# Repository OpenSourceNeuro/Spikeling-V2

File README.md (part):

<p align="left">

<h1 align="center"> Spikeling V 2.2</h1></p>
<h3 align="center">  A hardware implementation of spiking neurons for neuroscience teaching and outreach</h3></p>
<p align="center"><h6 align="right">developed by M.J.Y. Zimmermann, A.M. Chagas & T. Baden</h6></p>

<br></br>

This project is licensed under the [GNU General Public License v3.0](https://github.com/OpenSourceNeuro/Spikeling-V2/blob/main/LICENSE)<br>
The hardware is licensed under the [CERN OHL v1.2](https://github.com/OpenSourceNeuro/Spikeling-V2/blob/main/PCB%20-%202.2c/LICENSE)

***

<p style='text-align: justify;'>
Understanding how neurons encode and compute information is fundamental to our study of the brain, but opportunities for hands-on experience with neurophysiological techniques on living neurons are scarce in science education.

<p style='text-align: justify;'>
Due to budgetary constraints and logistical hurdles, few students can be afforded the opportunity to experience electrophysiological recordings on living neurons in action. Yet, a fundamental aspect of neuroscience courses is to understand electrical signalling within neurons and the transmission of signals across synapses, as well as the experimental techniques necessary to observe these properties.

<p style='text-align: justify;'>
To support university-level neuroscience teaching, we designed ‘Spikeling’, an open-source teaching support device that mimics the electrical properties of spiking neurons by running the computationally efficient yet versatile Izhikevich model.

<p style='text-align: justify;'>
It is an artificial neuron that can receive different inputs, integrate them and outputs its computation, just like a spiking neuron would!

<p style='text-align: justify;'>
Technically, it consists on a microcontroller (an ESP32) running the computationally efficient Izhikevich model of a spiking neuron.

<br>

<div>

<h6 align="center">Left: Rendering of spikeling electronic components. Right: Acrylic cover detailing spikeling functionalities.</h6>

</div>

<div>

<p style='text-align: justify;'>
The spikeling project emerged from local needs to teach neuroscience class modules for direct interaction with neuron physiology, data analysis, fluorescence imaging, protocol design, etc. The aim is to provide hands-on experience on how neurons encode information and how diverse variables modulates their activities, while engaging students with crucial aspects of data collection, experimental limitations, methodology and statistical analysis.

<p style='text-align: justify;'>
In order to give users a full interactive experience with the Spikeling neuron, a drawing engraved on the cover details in a neuro-morphic fashion all device functionalities. Furthermore, a spike-triggered LED and buzzer have been added to the device.

<p style='text-align: justify;'>
A dedicated GUI (Graphical User Interface) allows users to fully interact with Spikeling, plot all data generated and record them for further analysis.

<p style='text-align: justify;'>
Overall, Spikeling is a versatile device, allowing any teaching staff to conceive dry-lab tutorials or home assignments related to their own teaching course materials.

<p style='text-align: justify;'>
Enthusiasts and potential collaborators can source the electronic bits for this project from <a href="https://kitspace.org/boards/github.com/maxzimmer/spikeling-v2/">KitSpace</a></p>

</div>

***

<h2 align="center"> A brief summary of Spikeling functions</h3>

<br>

<div>

<h3 align="left"> Neurophysiology:</h3></p>

<p style='text-align: justify;'>
Spikeling is conceived on the Izhikevich model, which “reproduces spiking and bursting behaviour of known type of cortical neurons. The model combines the biologically plausibility of Hodgkin-Huxley-type dynamics and the computational efficiency of integrate-and-fire neurons” (E.M. Izhikevich, IEEE Transactions on Neural Networks, 2003, doi: 10.1109/TNN.2003.820440).

<p style='text-align: justify;'>
Students can appreciate playing with many variables that can be encountered in textbook or related to class material. A simulated patch-clamp experiment (represented by a pipette drawing on the top cover) allows students to “inject current” into the Spikeling neuron. They can furthermore modulate the amount of current injected, the speed and duration at which it is injected and observe the adaptation effect on a spiking neuron.

<p style='text-align: justify;'>
Spikeling also possesses a photodiode (modelized on the top cover as a photoreceptor) making Spikeling photo-sensitive. The photodiode mimics current inputs a photoreceptor would have on a spiking neuron. Students can appreciate the impact of a flash light onto the photoreceptor and investigate the different effects it may have. Ultimately, a supplied LED can be connected to the stimulus port and can then be controlled in frequency and intensity for controlled experiments. Advanced variable such as photoreceptor decay and recovery rate could also be investigated.

<p style='text-align: justify;'>
Each Spikeling unit possesses one “axonal” output and two “dendritic” inputs. Each dendritic input possesses a knob that can modulate the synaptic gain positively or negatively (mimicking excitatory and inhibitory synapses). In advanced stages, students could be encouraged to form neuronal networks. Auxiliary neurons can furthermore be stimulated synchronously from the “main neuron” experiment box to set a controlled environment.

</div>

<br>

<div>

<h6 align="center">Left: A Spikeling unit being stimulated by a direct current injection (blue cable) while receiving synaptic inputs from a second unit (pink cable). Right: Spikeling GUI displaying the unit membrane voltage (red trace) while being light-stimulated by a controlled LED (blue trace) which generates input current (green trace).</h6>

</div>

<br>

***

<br>

<div>

<h3 align="left"> Data analysis</h3></p>

<p style='text-align: justify;'>
Handling large dataset is an important part of daily academic work. However, few universities offer coding and programming modules for their neuroscience courses. A proper data analysis of any kind starts with the understanding of a program language and the understanding of every steps of the analysis pipeline. Only then, students can appreciate the results of their experiments and engage in their critical interpretation.

<p style='text-align: justify;'>
Any data generated by Spikeling can be saved and exported.  The GUI comes with a simple built-in data analysis that allows students to check their data and generate raster plots. From this simple analysis they could appreciate how neuronal information is encoded within stochastic spike trains (see below).

<p style='text-align: justify;'>
This simple analysis could be used for home assignments in the early stages of student degree before engaging them in developing their own analysis code.

<p style='text-align: justify;'>
For advanced data analysis and basic statistics, python notebooks are provided to serve as template for the teaching staff. It is our hope to create a Spikeling community where users could share courses, exercises and data analysis scripts to be widely used in neuroscience and coding courses.

</div>

<br>

<div>

<h6 align="center">GUI displaying the “Neuron Generator” page where users can appreciate the model underlying Spikeling activity and from which they can generate unique neuron to further run on Spikeling.</h6>

</div>

<br>

***

<br>

<div>

<h3 align="left">Stimulus generator:</h3>

<p style='text-align: justify;'>
Spikeling comes by default with a repeated square wave pattern stimulus, on which the user could only modulate the intensity and the frequency, might it be for direct current injection or light stimulation.

<p style='text-align: justify;'>
Here users are encouraged to develop their own stimulus (successive waves, sinusoidal loops, chirp, binary noise, etc.). Some basic stimuli are already available. The main point of this feature is to encourage the students to conceive their own experiments leading them to think about the protocol that needs to be implemented in order to answer the experimental questions they are being faced with.

</div>

<br>

<div>

<h6 align="center">GUI displaying the “Simulus Generator” page where users can generate their own unique stimuli. The left screen shows repetitive increments of current, as seen in classic electrophysiology experiments (10 steps with 10 a.u. current increment lasting 25 ms with a resting period of 5ms at 0 a.u. current). The right screen shows a sine wave stimulus (50 a.u. amplitude, 20 Hz frequency over a period of 250 ms and a resting period of 100 ms at 0 a.u. current)</h6>

</div>

<br>

***

<br>

<div>

<h3 align="left">Fluorescence imaging simulation:</h3>

<p style='text-align: justify;'>
Since Spikeling generates membrane voltage data, we could use this “ground truth data” to generate a simulated calcium concentration transient underlying spike occurrence in the neuron. And from then, use the later to model a simulated fluorescence.

<p style='text-align: justify;'>
Students could then be engaged into dynamic calcium fluorescence imaging (i.e two-photon microscopy) and play with many variables that could be encountered from the experimenter side (frame rate, laser power, photo detector gain, etc.), from the calcium concentration properties within the neuron (concentration baseline, decay, increase jump per spike, etc.)  or from the calcium indicator properties itself (indicator affinity, dissociation constant, brightness, photo-bleach, etc.).

<p style='text-align: justify;'>
For an even more realistic simulation, students could choose to move from a linear model to a non-linear saturation model of the fluorescence signal.

</div>

<br>

<div>

<h6 align="center">GUI displaying linear(left) and (non-linear) models of simulated fluorescence (green) based on simulated calcium concentration (pink)</h6>

</div>

<div>

<p style='text-align: justify;'>
Here, the aim is to familiarise students with the type of data they could encounter in their future academic work, incorporating noise and limitations to the data that are inherent to every experiments.

<p style='text-align: justify;'>
Ultimately, students could be encouraged to analyse imaging data, even implement spike inference algorithms and compare their results to the “ground truth data” that generated the fluorescence trace.

</div>

<br>

***

<br>

<div>

<h3 align="left">Exercises:</h3>

<p style='text-align: justify;'>
Spikeling comes with a set of suggested exercises that could be used in class as a guideline for the teaching staff to explore Spikeling functionalities. They are conceived to allow students to make a concrete connection between neurophysiology concepts seen in lectures with a responsive in silico model.

<p style='text-align: justify;'>
Exercises are also a mean to introduce some epistemology into the teaching material: Understanding how a neurobiology concept became a knowledge and how it can be tested, confirmed or refuted.
In advance courses, giving students the opportunity to design their own experiment as assignment also allows to introduce good methodology and protocol design practices. Which, unfortunately has shown to be too often mistaken with methods.

<p style='text-align: justify;'>
We would always encourage teachers to develop their own exercises based on the content they cover in class. It is our hope that such exercises could also be used as homework grading system.

</div>

<br>

***

<br>

<h2 align="center">Detailed Spikeling functions</h3></p>

<br>

- [Spikeling: A spiking neuron interface](#a-spiking-neuron-interface)
- [Spikeling: GUI - neuron parameters](#spikeling-gui-neuron-parameters)
- [Spikeling: GUI - stimuli parameters](#spikeling-gui-stimuli-parameters)
- [Spikeling: Data Analysis](#-data-analysis)
- [Spikeling: Neuron generator](#spikeling-neuron-generator)
- [Spikeling: Stimulus Generator](#stimulus-generator)
- [Spikeling: Multiple recording](#spikeling-multiple-recording)

<br>

- [Fluorescence: imaging simulation](#fluorescence-imaging-simulation)
- [Fluorescence: Imaging parameters](#fluorescence-imaging-parameters)
- [Fluorescence: Calcium parameters](#fluorescence-calcium-parameters)
- [Fluorescence: Fluorescence parameters](#fluorescence-imaging-parameters)
- [Fluorescence: Data Analysis](#fluorescence-data-analysis)
- [Fluorescence: Multiple fluorescence](#fluorescence-multiple-fluorescence)

<br>

- [Exercices: GUI](#exercises-gui)
- [Exercices: Python](#exercises-python)

<br>

- [GitHub Contributions](#gitHub-Contributions)

- [Arduino code and libraries](#)

- [GUI PyQt6 / PySide6 script](#)

<br>

***

<br>

## A spiking neuron interface

<br>

<p style='text-align: justify;'>
The entire layout of the Spikeling board has been reconceived and a laser-cut acrylic sheet repesenting a neuron now sits on top of the board. All ports and potentiometers are now strategically placed.

<p style='text-align: justify;'>
The ESP32 is placed below the soma, the synaptic inputs from other Spikeling units are placed on the left, the synaptic output is placed on the right. Along the axon now sits a RGB LED, the red LED brightness follows as before the Vm status of the neuron, and the LED sparks in white when the neuron spike. The spike buzzer also sit along the axon, a small hole on the acrylic sheet sitting just above so the click can be heard coming from that direction. Both indicators can now be disabled by users at their pleasure.

<p style='text-align: justify;'>
The Vm potentiometer and the Current-in port are now grouped together and sit on the acrylic sheet at the bottom of an electrode pipette. They can now be considered as patch clamp experiment variables.

<p style='text-align: justify;'>
A photoreceptor is now drawn on the acrylic sheet, below the opsin sits a photodiode, and a potentiometer on the photoreceptor body now controls the photoreceptor sensitivity and its polarity (users can thus decide if the photoreceptor has an excitatory or an inhibitory effect on the neuron)

<p style='text-align: justify;'>
The noise potentiometer now sits in a box by itself as it represents parasitic noise from the experiment environment (synaptic inputs, receptor noise, thermal noise, experimental setup, etc.) and is independent from the rest of the Spikeling functions. This potentiometer is different from the others: it is not center-detented as it generates noise from a zero to a maximum value.

<p style='text-align: justify;'>
Next is the Neuron mode box which contains the twelve available modes to the users and a push button that allows the user to switch between them.

<p style='text-align: justify;'>
Finally, the last box contains all experimental tools allowing stimuli generation. As detailed on the acrylic top cover, the user can control the stimulus frequency and the stimulus intensity, along with its polarity. The stimulus output can either be directly connected to the current-in port to simulate a current applied to a patched neuron through the pipette; or be connected to a cable with a 5mm LED soldered at its tip which can be placed directly on top of the photoreceptor opsin (photodiode below). The photoreceptor potentiometer allows to modulate the gain and polarity of the light-induced input current. Furthermore, the photoreceptor possesses functions (on the GUI: decay/recovery) simulating how a variety of photoreceptors would integrate a light stimuli and how it will adapt to prolonged stimulation.  

<br>

***

<br>

<p style='text-align: justify;'>
Spikeling now possesses its own GUI, written in python and using the latest PyQt6/PySide6 library. The script then uses pyInstaller so it can be translated into a windows/linux/mac app, ready to be easily distributed to users.

<br>

<p style='text-align: justify;'>
The GUI is divided into distinct pages. The first one is the main GUI window where users connect the board to the computer. From there they can choose to either select the neuronal mode on the board directly (neuron mode box) or through the GUI (note that custom modes will have to be selected from here, and in this instance the GUI takes priority over the board commands).

<p style='text-align: justify;'>
The main window displays the Spikeling activity (Neuron Vm, total current input from all sources & stimulus ). If connected to other Spikelings, the GUI can display synaptic inputs: their incoming neuron Vm and their spiking events, which will be translated into input current for the main neuron. Traces can be selected through checkbox and superimposed over the same graph with a common timeline.

<p style='text-align: justify;'>
The "Neuron Mode" defines the current Izhikevich model being used [see Neuron Generator](#Spikeling-Neuron-generator). Twelve are encoded by default on the Spikeling unit and can be chosen either from the board itself or directly from the GUI: "Select Neuron Mode". Note that any command from the GUI will take priority over the board. Custom Neuron Modes can be selected from here and upload to the board.

<p style='text-align: justify;'>
The neuron interface page also possesses two buttons to enable/disable the spike buzzer sound and the spike LED, which in a class room full of spikeling, are regarded as huge relieves.

<p style='text-align: justify;'>
Below the main window, sits the recording window. All last generated data from traces that are checked on the main window will be saved in a .csv format.

<p style='text-align: justify;'>
On the right hand side two control columns can be found. For all commands, when the toggle button is enabled, the GUI takes over the potentiometer and controls directly the Spikeling variables. This allows users to design an experimental protocol in a controlled fashion.

<br>

***

<br>

<p style='text-align: justify;'>
Spikeling membrane voltage (Vm), displayed on the GUI in red, is generated by the Izhikevich model equation.
It is rather simple and relies on four parameters [see Neuron Generator](#Spikeling-Neuron-generator).

<br>

<p style='text-align: justify;'>
When Vm > 30mV, then a spike is generated, both the spike LED and spike buzzer on the board are activated, and the Vm model is reset accordingly (see above).

<p style='text-align: justify;'>
The green trace represents all current inputs received by the board and summed up in the variable "I" in the Izhikevich equation.
These current inputs correspond to the synaptic inputs, the direct current injection from the patch clamp port or the light induced current from the photodiode, and the noise generator potentiometer. All will influence the Vm equation and the subsequent spiking pattern.

<p style='text-align: justify;'>
The blue trace represents the square wave stimulus, which can be manually modulated in length, intensity and polarity through the potentiometer located in the "experiment box". The resulting stimulus signal is sent to the "Stimulus Output" port.
A jack cable connecting the "Stimulus Output" port to the "Current In" port will deliver the stimulus signal directly into the Spikeling neuron, simulating a direct current injection through a patched clamp electrode.
If a LED is connected to the "Stimulus Output" port and placed onto the photodiode, then the "photoreceptor" is stimulated accordingly and generates a current that will in turn be injected into the Izhikevich equation.

<p style='text-align: justify;'>
Users can also interact with the "Current In" potentiometer placed on the electrode and constantly inject steady current in order to either hyperpolarise or depolarise Spikeling.
Users can also interact with the "Photo-Gain" potentiometer and modulate the light sensitivity and polarity of the photodiode, thus generating ON/OFF neurons.

<p style='text-align: justify;'>
If Spikeling is connected to other units, the main window can display their Vm and their synaptic current inputs. Users can modulate these inputs by interacting with the "Synapse Gain" potentiometers which modulate the intensity and polarity of the synaptic inputs, giving rise to excitatory and inhibitory synapses.

<p style='text-align: justify;'>
Furthermore, users can stimulate the auxiliary Spikeling units in synchrony via the main unit's "Stimulus Output" port by using a splitter audio jack

<br>

***

<br>

## Spikeling GUI neuron parameters

<br>

TBC

<br>

***

<br>

## Spikeling GUI stimuli parameters

<br>

TBC

<br>

***

<br>

## Spikeling Neuron generator

<br>

<p style='text-align: justify;'>
Spikeling GUI comes with a "Neuron Generator" page where users can interact with the Izhikevich equation, understand the model generating Spikeling membrane voltage, and create their own "neuron mode" to be loaded on the main page.

<p style='text-align: justify;'>
The main window computes the Izhikevich model with a modifiable current input. Users can change the 4 variable of the code and display the resulting "neuron mode". This is also where users can come up with their own neuronal modes to experiment on. This is also where teachers can generate their own custo-made neuron, save them, and impose them as experimental model for, i.e. home assignments.

<p style='text-align: justify;'>
From <a href="https://pubmed.ncbi.nlm.nih.gov/18244602">Izhikevich publication</a>:
<em> Bifurcation methodologies enable us to reduce many biophysically accurate Hodgkin–Huxley-type neuronal models to a two-dimensional (2-D) system of ordinary differential equations of the form:</em>

```math
v' = 0.04v^2 + 5v + 140 - u + I
```
```math
u' = a * (bv - u)
```

With the auxiliary after-spike resetting:

<p align="center">
if:
</p>

```math
v >= 30mV
```
<p align="center">
 then:
 </p>

 ```math
 v = c
 ```

<p align="center">
 and:
 </p>

 ```math
 u = u + d
```

<br>

<p style='text-align: justify;'>
Here, v and u are dimensionless variables, and a, b, c, and d are dimensionless parameters, and '= d/dt, where t is the time (0.1 µs).

<p style='text-align: justify;'>
The variable v represents the membrane potential of the neuron and u represents a membrane recovery variable, which accounts for the activation of K+ ionic currents and inactivation of Na+ ionic currents, and it provides negative feedback to v.

<p style='text-align: justify;'>
After the spike reaches its apex (+30 mV), the membrane voltage and the recovery variable are reset.
Synaptic currents or injected DC-currents are delivered via the variable I.

<p style='text-align: justify;'>
Below the stimulus frequency and strength sliders can be found a custom stimulus display. Here the user can choose to use instead of the classical square wave, either a stimulus from a pre-design library (comprising sine wave, chirp, white noise, etc.), or either a custom made stimulus generated from the GUI "stimulus generator" tab.

<br>

***

<br>

## Spikeling Stimulus Generator

<br>

<p style='text-align: justify;'>
Spikeling GUI also comes with a "Stimulus Generator" page where users can generate their own stimuli. In the current version seven distinct stimulus pattern are available with various parameters to interact with.
All stimuli can then be saved and further loaded from the Spikeling main window.

<br>

<div>

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
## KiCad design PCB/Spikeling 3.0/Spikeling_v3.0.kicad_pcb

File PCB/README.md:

<h1 align="center"> Spikeling v2 - Assembly Manual</h1></p>

<br></br>

## Overview

<p align="justify">
This page contains detailed assembly instructions for both version of La Spikeling unit, and includes a parts list for purchasing all electronics components.
Instructions on how to upload and update the microcontroller code and how to calibrate the device can be found <a href="https://github.com/OpenSourceNeuro/Spikeling-V2/tree/main/Instruction%20Manual"> <strong>on the instruction manual</strong> </a>.
Instructions regarding the GUI and on how to design stimuli can be found <a href="https://github.com/OpenSourceNeuro/LED-Zappelin-V2/blob/main/GUI_UserManual.md"><strong>here</strong></a>
</p>

***

- [Ordering PCB](#Ordering-the-PCB)
- [Assembling Spikeling](#Assembly)
- [Acrylic Covers](#Acrylic-Covers)

***

## Ordering the PCB

<p align="justify">
First step consist in getting the printed circuit board (PCB).
The PCB source files were designed on <a href="http://kicad.org/">KiCAD 9.0</a> and are available here to be modified by users if need be.
Users can find the "Gerber" files (zipped in the gerber folder) that companies (i.e. <a href="https://jlcpcb.com">JLCPCB</a>) will request to manufacture PCBs.
</p>

<br></br>

***
***

## Assembly

## Acrylic Covers

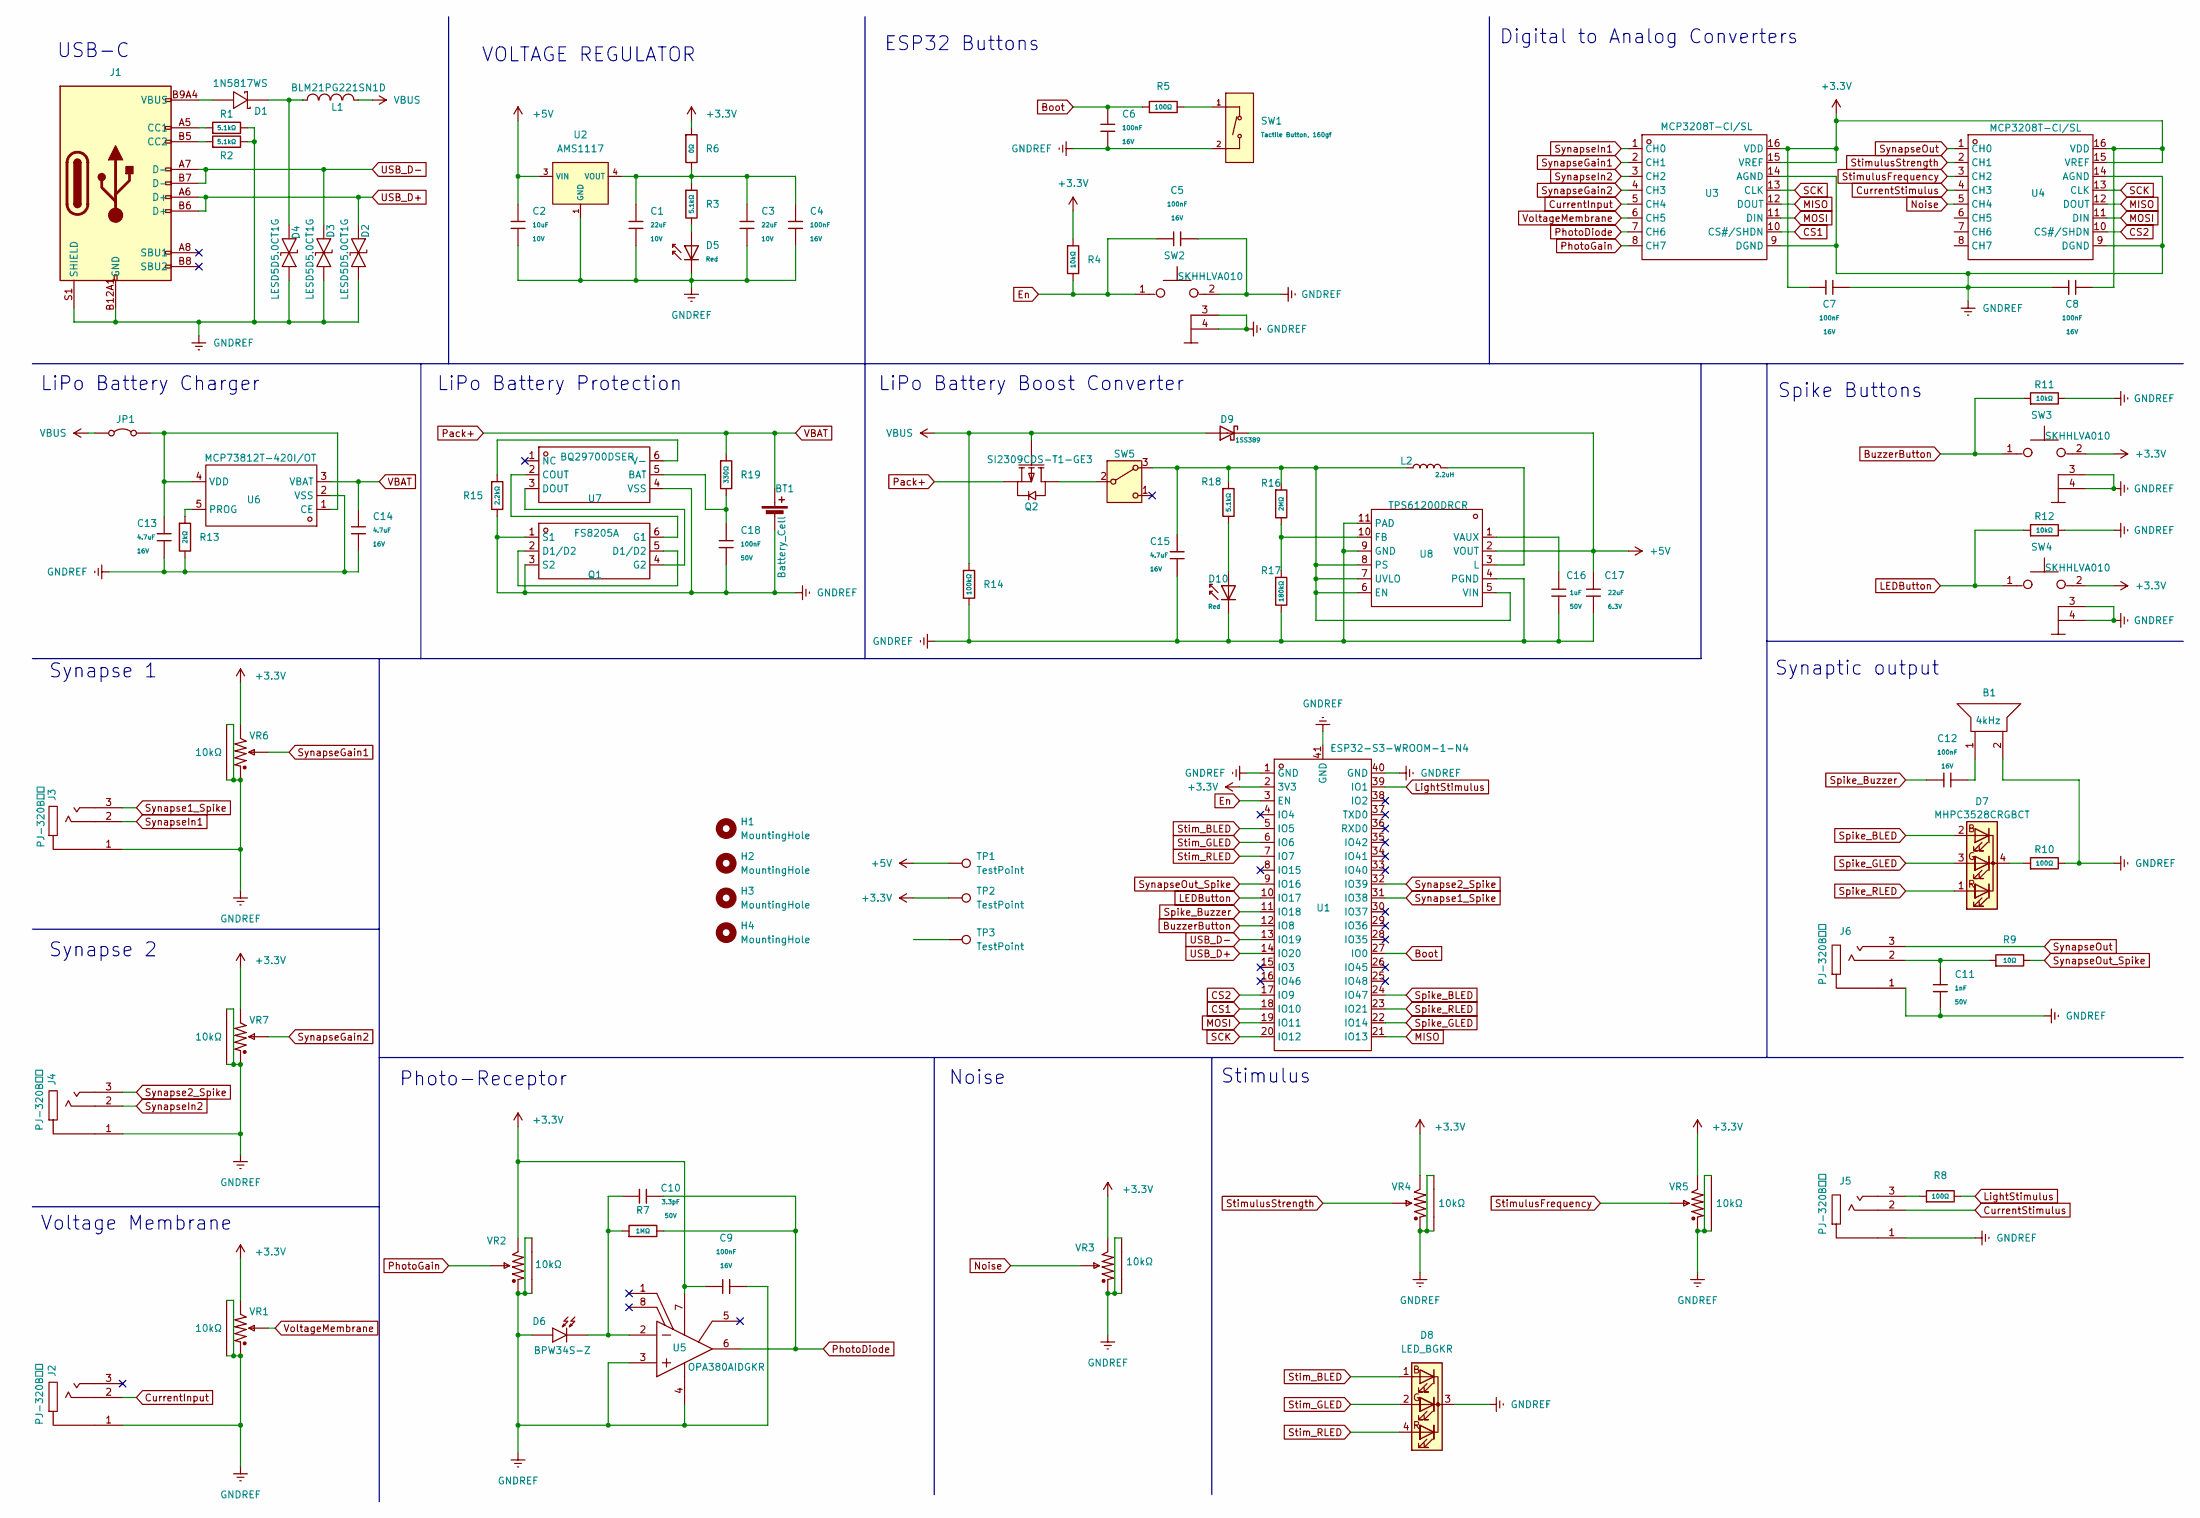
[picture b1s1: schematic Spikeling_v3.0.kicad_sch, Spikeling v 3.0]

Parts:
B1: 4kHz; BUZ-TH_L12.0-W12.0; VOLTAGE RATING 5V; MANUFACTURER PART KMTG1203; LCSC PART NAME KMTG1203 工业级-压电式无源贴片蜂鸣器
BT1: Battery_Cell; JST_XH_B2B-XH-A_1x02_P2.50mm_Vertical
C1, C3: 22uF; C_1206; Voltage Rated 10V; Tolerance ±10%; Part CL31A226KPHNNNE; LCSC C5672
C2: 10uF; C_0603; Voltage Rated 10V; Tolerance ±10%; Part CL10A106KP8NNNC; LCSC C19702
C4, C5, C6, C7, C8, C9, C12: 100nF; C_0402; Voltage Rated 16V; Tolerance ±10%; Part CL05B104KO5NNNC; LCSC C1525
C10: 3.3pF; C_0402; Voltage Rated 50V; Part 0402CG3R3C500NT; LCSC C1565
C11: 1nF; C_0603; Voltage Rated 50V; Tolerance ±10%; Part CL10B102KB8NNNC; LCSC C1588
C13, C14, C15: 4.7uF; C_0603; Voltage Rated 16V; Tolerance ±10%; Part CL10A475KO8NNNC; LCSC C19666
C16: 1uF; C_0603; Voltage Rated 50V; Tolerance ±10%; Part CL10A105KB8NNNC; LCSC C15849
C17: 22uF; C_0603; Voltage Rated 6.3V; Tolerance ±20%; Part CL10A226MQ8NRNC; LCSC C59461
C18: 100nF; C_0603; Voltage Rated 50V; Tolerance ±10%; Part CC0603KRX7R9BB104; LCSC C14663
D1: 1N5817WS; SOD-323_L1.8-W1.3-LS2.5-RD; FORWARD VOLTAGE (VF@IF) 750mV@3.1A; REVERSE VOLTAGE (VR) 20V; MANUFACTURER PART 1N5817WS; LCSC PART NAME 电压:20V 电流:1A
D2, D3, D4: LESD5D5.0CT1G; SOD-523_L1.2-W0.8-LS1.6-BI; CLAMPING VOLTAGE 18.6V; VOLTAGE - BREAKDOWN 5.6V; MANUFACTURER PART LESD5D5.0CT1G; LCSC PART NAME 双向ESD
D5, D10: Red; D_0603; Part KT-0603R; LCSC C2286
D6: BPW34S-Z; SENSOR-TH_BPW34S-Z; MANUFACTURER PART BPW34S-Z; LCSC PART NAME 920nm 频谱范围420nm~1120nm 反向电压32V
D7: MHPC3528CRGBCT; LED-SMD_4P-L3.2-W2.8-BL; LCSC PART NAME RGB三色 正贴
D8: LED_BGKR; LED_D5.0mm-4_RGB_Wide_Pins
D9: 1SS389; D_SOD-523; Part 1SS389; LCSC C22466369
H1, H2, H3, H4: MountingHole; MountingHole_3mm
J1: Connector, USB-TYPE-C-16P; TYPE-C-SMD_HX-TYPE-C-16PIN; LCSC C2927039
J2, J3, J4, J5, J6: PJ-320B贴片; AUDIO-SMD_PJ-320B; CURRENT RATING (MAX) 200mA; VOLTAGE RATING (MAX) 30V; MANUFACTURER PART PJ-320B贴片; LCSC PART NAME 3.5mm耳机座
JP1: Jumper; SolderJumper-2_P1.3mm_Open_Pad1.0x1.5mm
L1: BLM21PG221SN1D; L0805; TOLERANCE ±25%; CURRENT RATING 2A; MANUFACTURER PART BLM21PG221SN1D; LCSC PART NAME 单路 0805磁珠 阻抗220Ω@100MHz
L2: 2.2uH; L_0805; Tolerance ±10%; Part CMI201209U2R2KT; LCSC C1043
Q1: FS8205A; SOT-23-6; MANUFACTURER PART FS8205A; LCSC PART NAME 2个N沟道 耐压:20V 电流:6A
Q2: SI2309CDS-T1-GE3; SOT-23-3_L2.9-W1.3-P1.90-LS2.4-BR; MANUFACTURER PART SI2309CDS-T1-GE3; LCSC PART NAME 1个P沟道 耐压:60V 电流:1.6A
R1, R2, R3, R18: 5.1kΩ; R_0603; Overload Voltage (Max) 75V; Tolerance ±1%; Part 0603WAF5101T5E; LCSC C23186
R4, R11, R12: 10kΩ; R_0603; Overload Voltage (Max) 75V; Tolerance ±1%; Part 0603WAF1002T5E; LCSC C25804
R5, R8, R10: 100Ω; R_0603; Overload Voltage (Max) 75V; Tolerance ±1%; Part 0603WAF1000T5E; LCSC C22775
R6: 0Ω; R_0603; Overload Voltage (Max) 75V; Tolerance ±1%; Part 0603WAF0000T5E; LCSC C21189
R7: 1MΩ; R_0603; Overload Voltage (Max) 75V; Tolerance ±1%; Part 0603WAF1004T5E; LCSC C22935
R9: 10Ω; R_0603; Overload Voltage (Max) 75V; Tolerance ±1%; Part 0603WAF100JT5E; LCSC C22859
R13: 2kΩ; R_0603; Overload Voltage (Max) 75V; Tolerance ±1%; Part 0603WAF2001T5E; LCSC C22975
R14: 100kΩ; R_0603; Overload Voltage (Max) 75V; Tolerance ±1%; Part 0603WAF1003T5E; LCSC C25803
R15: 2.2kΩ; R_0603; Overload Voltage (Max) 75V; Tolerance ±1%; Part 0603WAF2201T5E; LCSC C4190
R16: 2MΩ; R_0603; Overload Voltage (Max) 75V; Tolerance ±1%; Part 0603WAF2004T5E; LCSC C22976
R17: 180kΩ; R_0603; Overload Voltage (Max) 75V; Tolerance ±1%; Part 0603WAF1803T5E; LCSC C22827
R19: 330Ω; R_0603; Overload Voltage (Max) 75V; Tolerance ±1%; Part 0603WAF3300T5E; LCSC C23138
SW1: Tactile Button, 160gf; SW_TS-1088-AR02016; Voltage Rating (Dc) 12V; Part TS-1088-AR02016; LCSC C720477
SW2, SW3, SW4: SKHHLVA010; KEY-TH_4P-L7.5-W6.8-P4.50-LS7.2; VOLTAGE RATING (DC) 12V; MANUFACTURER PART SKHHLVA010; LCSC PART NAME 6*6*5.85mm 卧插 轻触开关
SW5: SW_Nidec_CAS-120A1; SW-TH_MMP122-R
TP1, TP2, TP3: TestPoint; TestPoint_Pad_D2.0mm
U1: ESP32-S3-WROOM-1-N4; WIFIM-SMD_ESP32-S3-WROOM-1-N8; MANUFACTURER PART ESP32-S3-WROOM-1-N4; LCSC PART NAME 通用型Wi-Fi+低功耗蓝牙MCU模组
U2: AMS1117; SOT-223-3_L6.5-W3.4-P2.30-LS7.0-BR; Output Voltage 3.3V; Dropout Voltage 1.3V@(800mA); Part AMS1117-3.3; LCSC C6186
U3, U4: MCP3208T-CI/SL; SOIC-16_L9.9-W3.9-P1.27-LS6.0-BL; VOLTAGE - SUPPLY 2.7V~5.5V; MANUFACTURER PART MCP3208T-CI/SL; LCSC PART NAME MCP3208T-CI/SL
U5: OPA380AIDGKR; VSSOP-8_L3.0-W3.0-P0.65-LS4.9-BL; MANUFACTURER PART OPA380AIDGKR; LCSC PART NAME OPA380AIDGKR
U6: MCP73812T-420I/OT; SOT-23-5_L3.0-W1.7-P0.95-LS2.8-BR; VOLTAGE - SUPPLY 3.75V~6V; MANUFACTURER PART MCP73812T-420I/OT; LCSC PART NAME 单节锂离子/聚合物电池充电管理控制器
U7: BQ29700DSER; WSON-6_L1.5-W1.5-P0.50-TL; VOLTAGE - SUPPLY -300mV~8V; MANUFACTURER PART BQ29700DSER; LCSC PART NAME BQ29700DSER
U8: TPS61200DRCR; VSON-10_L3.0-W3.0-P0.50-TL-EP_TPS62410DRCR; VOLTAGE - SUPPLY 300mV~5.5V; OUTPUT VOLTAGE 1.8V~5.5V; MANUFACTURER PART TPS61200DRCR; LCSC PART NAME 低输入电压同步升压转换器
VR1, VR2, VR4, VR5, VR6, VR7: 10kΩ; RES-TH_RK09D1130C2P; TOLERANCE ±20%; VOLTAGE RATING 20V; MANUFACTURER PART RK09D1130C3C; LCSC PART NAME 10kΩ ±20%
VR3: 10kΩ; RES-TH_RK09D1130C2P; TOLERANCE ±20%; MANUFACTURER PART RK09D1130C2P; LCSC PART NAME 10kΩ ±20%

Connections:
+3.3V: C7.1, C8.2, C9.1, R4.1, R6.1, SW3.2, SW4.2, TP2.1, U1.2 (3V3), U3.15 (VREF), U3.16 (VDD), U4.15 (VREF), U4.16 (VDD), U5.7 (V+), VR1.3, VR2.3, VR3.3, VR4.3, VR5.3, VR6.3, VR7.3
+5V: C2.1, C17.1, D9.1, TP1.1, U2.3 (VIN), U8.2 (VOUT)
Boot: C6.1, R5.1, U1.27 (IO0)
BuzzerButton: R11.1, SW3.1, U1.12 (IO8)
CS1: U1.18 (IO10), U3.10 (CS#/SHDN)
CS2: U1.17 (IO9), U4.10 (CS#/SHDN)
CurrentInput: J2.2, U3.5 (CH4)
CurrentStimulus: J5.2, U4.4 (CH3)
En: C5.1, R4.2, SW2.1, U1.3 (EN)
LEDButton: R12.1, SW4.1, U1.10 (IO17)
LightStimulus: R8.2, U1.39 (IO1)
MISO: U1.21 (IO13), U3.12 (DOUT), U4.12 (DOUT)
MOSI: U1.19 (IO11), U3.11 (DIN), U4.11 (DIN)
unnamed: B1.1, C12.2
unnamed: C1.1, C3.1, C4.1, R3.1, R6.2, U2.2 (VOUT), U2.4 (VOUT)
unnamed: C11.1, J6.2, R9.1
unnamed: D1.1, D4.1, L1.1
unnamed: D1.2, J1.A9B4 (VBUS), J1.B9A4 (VBUS)
unnamed: D5.2, R3.2
unnamed: C10.2, D6.2 (C), R7.1, U5.2 (IN-)
unnamed: D7.4 (K), R10.1
unnamed: D10.2, R18.2
unnamed: J1.A5 (CC1), R1.1
unnamed: J1.B5 (CC2), R2.1
unnamed: J5.3, R8.1
unnamed 25: C13.1, JP1.2 (B), U6.1 (CE), U6.4 (VDD); also elsewhere on the board
unnamed: Q1.2 (D1/D2), Q1.5 (D1/D2)
unnamed: Q1.6 (G1), U7.2 (COUT)
unnamed: Q1.4 (G2), U7.3 (DOUT)
unnamed: Q2.3 (D), SW5.2 (B)
unnamed: R5.2, SW1.1 (A)
unnamed: R13.1, U6.5 (PROG)
unnamed: C18.1, R19.2, U7.5 (BAT)
unnamed: R16.2, R17.1, U8.10 (FB)
unnamed: L2.2, U8.3 (L)
unnamed: C16.1, U8.1 (VAUX)
Noise: U4.5 (CH4), VR3.2
Pack+: BT1.1 (+), C14.1, Q2.2 (S), R19.1, U6.3 (VBAT); also elsewhere on the board
PhotoDiode: C10.1, R7.2, U3.7 (CH6), U5.6 (OUT)
PhotoGain: U3.8 (CH7), VR2.2
SCK: U1.20 (IO12), U3.13 (CLK), U4.13 (CLK)
Spike_BLED: D7.2 (BA), U1.24 (IO47)
Spike_Buzzer: C12.1, U1.11 (IO18)
Spike_GLED: D7.3 (GA), U1.22 (IO14)
Spike_RLED: D7.1 (RA), U1.23 (IO21)
Stim_BLED: D8.1 (BA), U1.5 (IO5)
Stim_GLED: D8.2 (GA), U1.6 (IO6)
Stim_RLED: D8.4 (RA), U1.7 (IO7)
StimulusFrequency: U4.3 (CH2), VR5.2
StimulusStrength: U4.2 (CH1), VR4.2
Synapse1_Spike: J3.3, U1.31 (IO38)
Synapse2_Spike: J4.3, U1.32 (IO39)
SynapseGain1: U3.2 (CH1), VR6.2
SynapseGain2: U3.4 (CH3), VR7.2
SynapseIn1: J3.2, U3.1 (CH0)
SynapseIn2: J4.2, U3.3 (CH2)
SynapseOut: J6.3, U4.1 (CH0)
SynapseOut_Spike: R9.2, U1.9 (IO16)
USB_D+: D2.1, J1.A6 (D+), J1.B6 (D+), U1.14 (IO20)
USB_D-: D3.1, J1.A7 (D-), J1.B7 (D-), U1.13 (IO19)
VBUS: D9.2, JP1.1 (A), L1.2, Q2.1 (G), R14.1
VoltageMembrane: U3.6 (CH5), VR1.2

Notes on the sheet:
Spike Buttons
LiPo Battery Charger
Synapse 1
ESP32 Buttons
Synapse 2
LiPo Battery Boost Converter
Digital to Analog Converters
USB-C
Voltage Membrane
LiPo Battery Protection
Noise
Stimulus
VOLTAGE REGULATOR
Photo-Receptor
Synaptic output

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
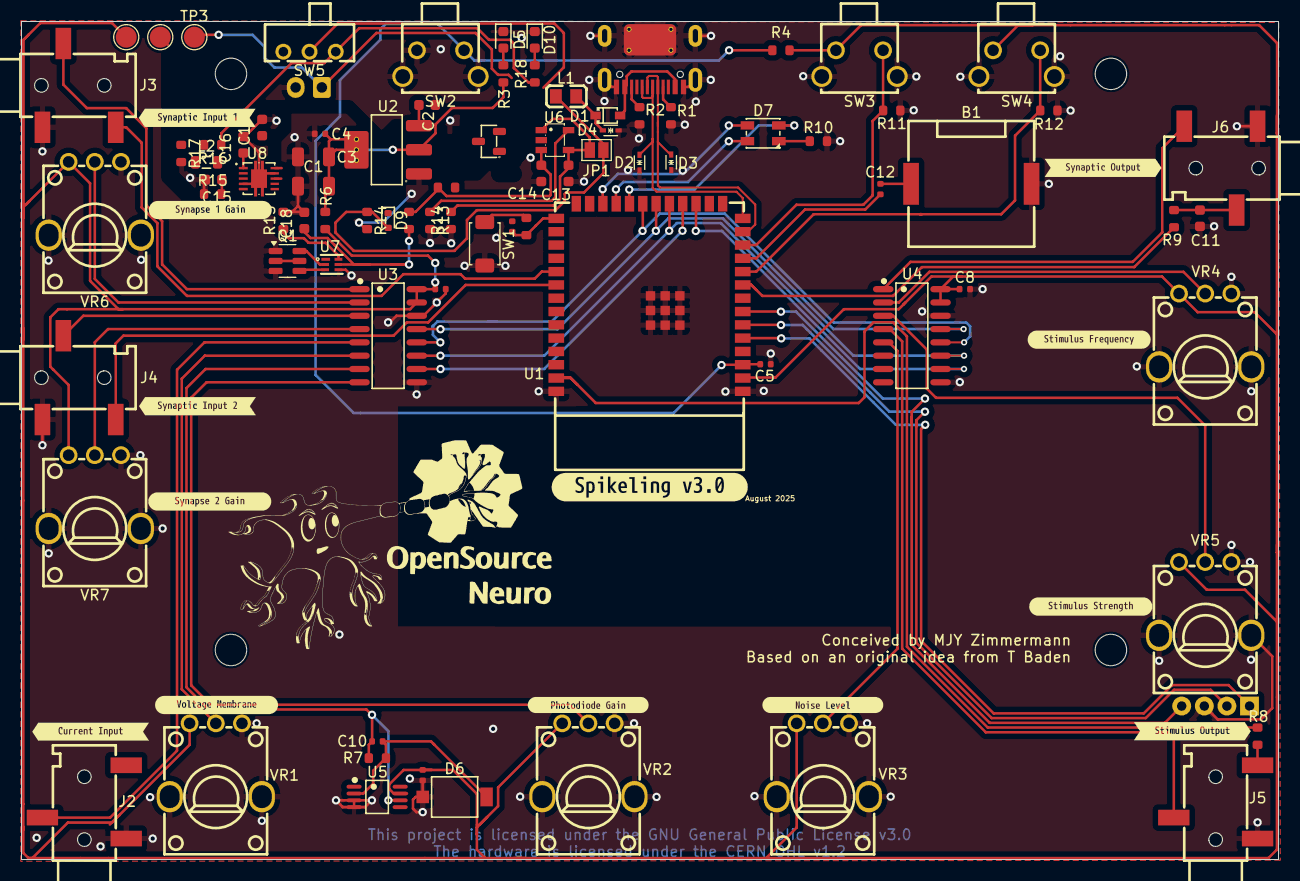
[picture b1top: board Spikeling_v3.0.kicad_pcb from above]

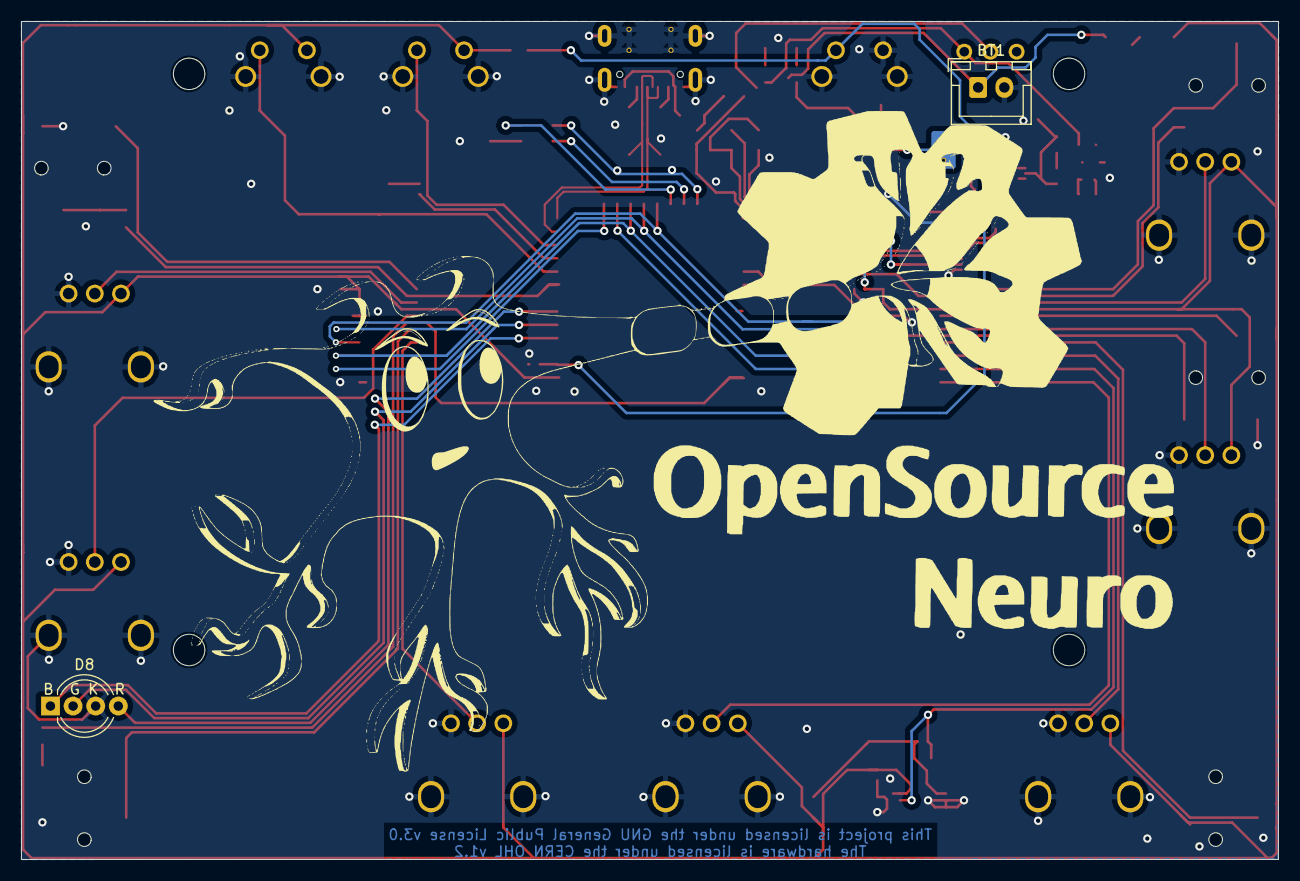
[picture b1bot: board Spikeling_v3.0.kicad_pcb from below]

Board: 2 copper layers, 120.0 x 80.0 mm, 105 parts (2 on the bottom side), 65 nets.

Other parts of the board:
.: Spikeling_neuron; Spikeling_Photoreceptor
.#2: Spikeling_neuron; Spikeling_Neuron
R14#2: 10kΩ; R_0603
R15#2: 2.2kΩ; R_0603
R21: 100kΩ; R_0603
kibuzzard-689381E8: G***; kibuzzard-689381E8
kibuzzard-689382F1: G***; kibuzzard-689382F1
kibuzzard-689383B5: G***; kibuzzard-689383B5
kibuzzard-689383D8: G***; kibuzzard-689383D8
kibuzzard-689384BB: G***; kibuzzard-689384BB
kibuzzard-6893830F: G***; kibuzzard-6893830F
kibuzzard-6893831F: G***; kibuzzard-6893831F
kibuzzard-6893832F: G***; kibuzzard-6893832F
kibuzzard-6893833B: G***; kibuzzard-6893833B
kibuzzard-68938301: G***; kibuzzard-68938301
kibuzzard-68938370: G***; kibuzzard-68938370
kibuzzard-68938494: G***; kibuzzard-68938494
kibuzzard-68972704: G***; kibuzzard-68972704

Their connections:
unnamed 25: R14#2.2; also elsewhere on the board
Pack+: R21.2; also elsewhere on the board

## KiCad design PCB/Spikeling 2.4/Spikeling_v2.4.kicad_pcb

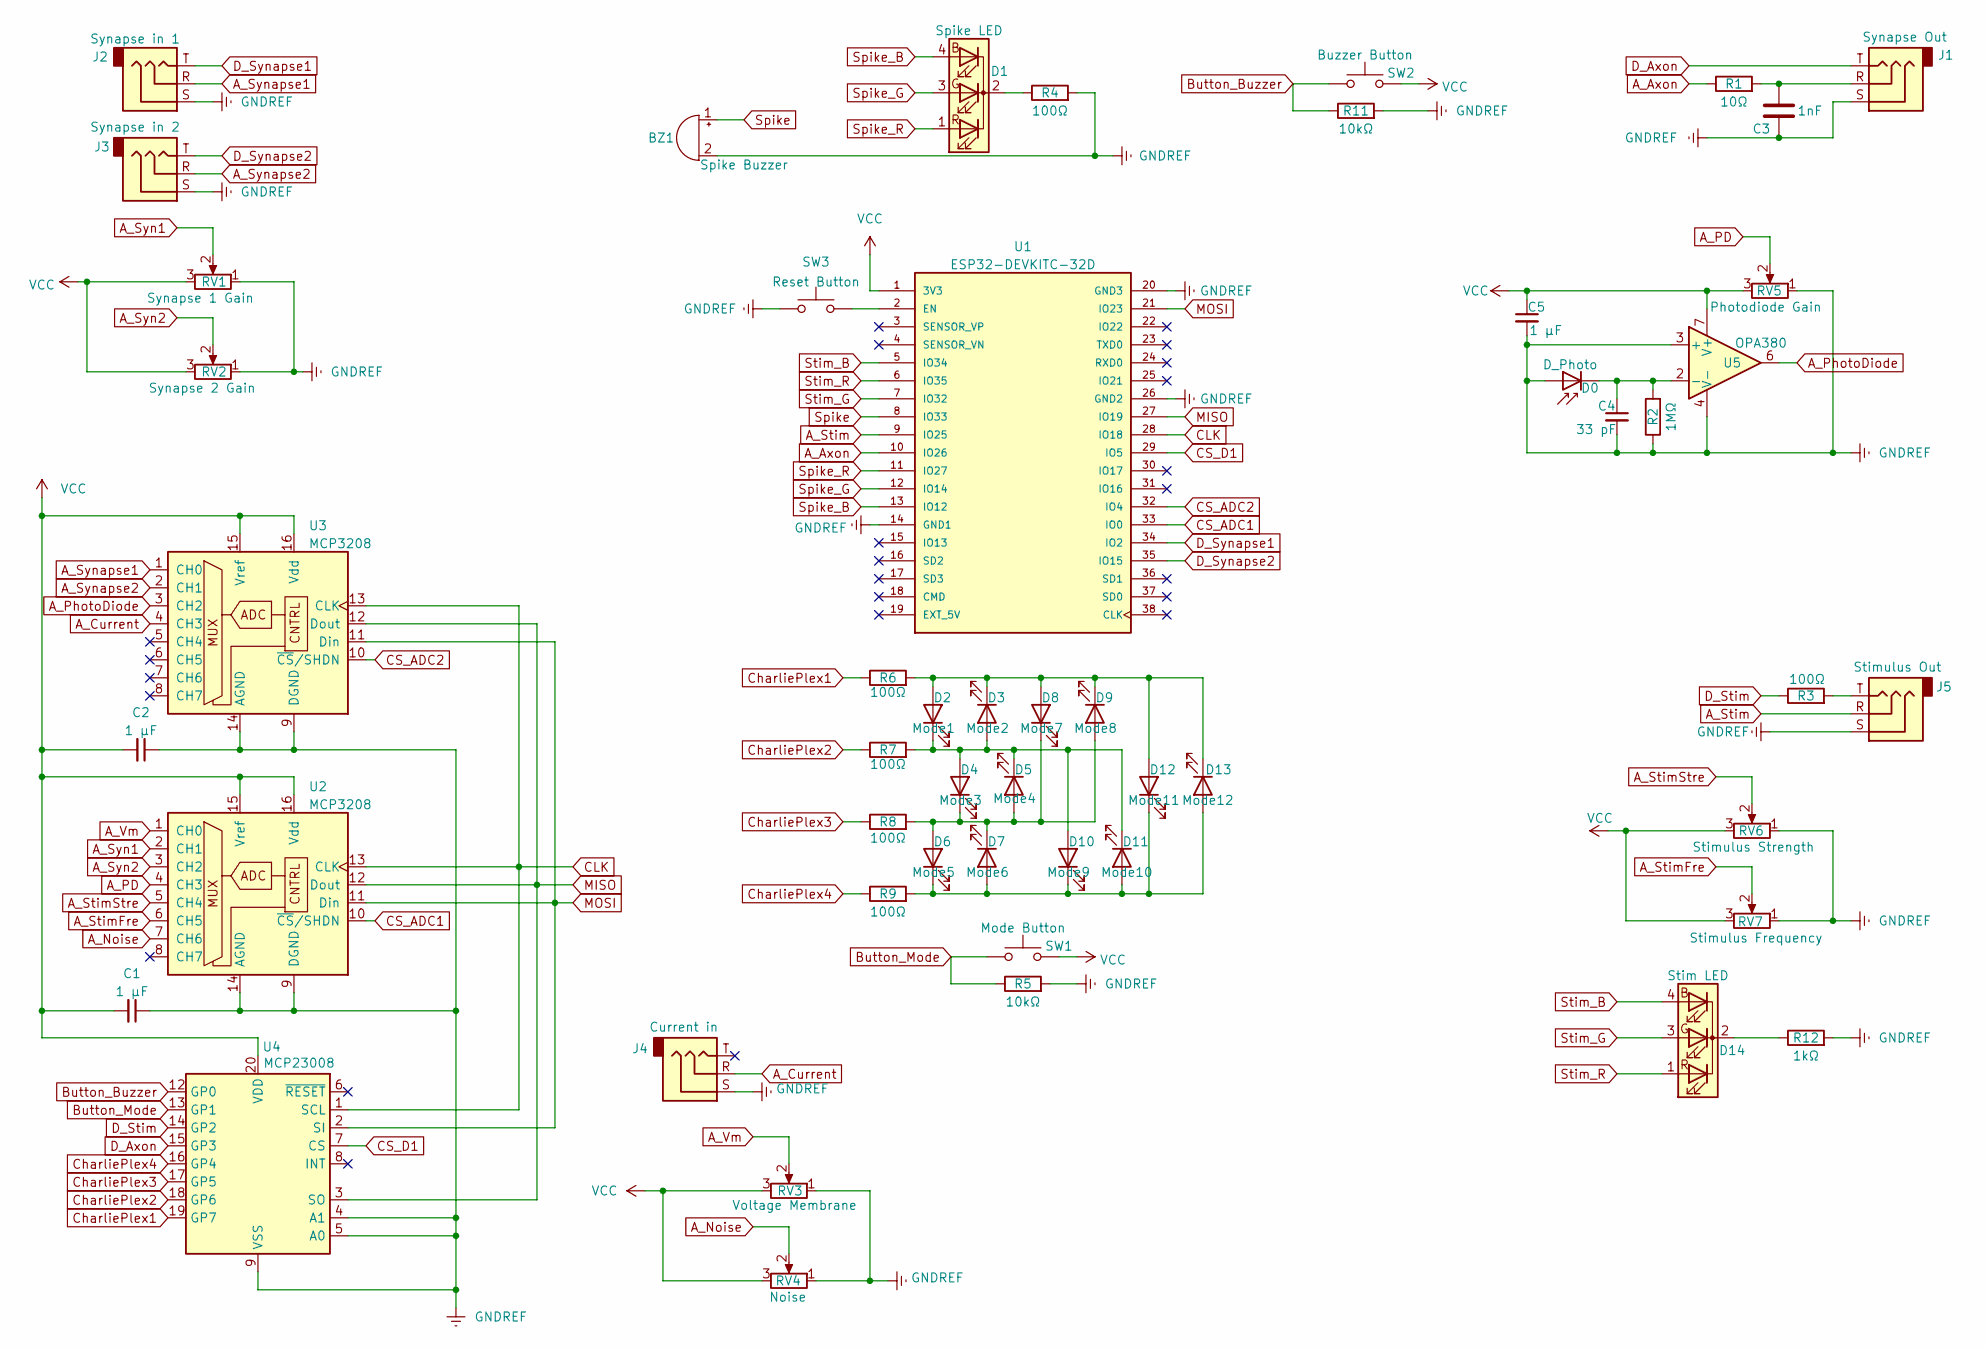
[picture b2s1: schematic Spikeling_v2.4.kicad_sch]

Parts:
BZ1: Spike Buzzer; Buzzer_11.5x9.5RM5
C1, C2, C5: 1 μF; CP_Radial_D4.0mm_P2.00mm
C3: 1nF; CP_Radial_D4.0mm_P2.00mm
C4: 33 pF; CP_Radial_D4.0mm_P2.00mm
D0: D_Photo; LED_D5.0mm
D1: Spike LED; LED_D5.0mm-4_RGB
D2: Mode1; LED_D3.0mm
D3: Mode2; LED_D3.0mm
D4: Mode3; LED_D3.0mm
D5: Mode4; LED_D3.0mm
D6: Mode5; LED_D3.0mm
D7: Mode6; LED_D3.0mm
D8: Mode7; LED_D3.0mm
D9: Mode8; LED_D3.0mm
D10: Mode9; LED_D3.0mm
D11: Mode10; LED_D3.0mm
D12: Mode11; LED_D3.0mm
D13: Mode12; LED_D3.0mm
D14: Stim LED; LED_D5.0mm-4_RGB
J1: Synapse Out; Spikeling Audio Jack 3.5mm
J2: Synapse in 1; Spikeling Audio Jack 3.5mm
J3: Synapse in 2; Spikeling Audio Jack 3.5mm
J4: Current in; Spikeling Audio Jack 3.5mm
J5: Stimulus Out; Spikeling Audio Jack 3.5mm
R1: 10Ω; R_Axial_DIN0207_L6.3mm_D2.5mm_P10.16mm_Horizontal
R2: 1MΩ; R_Axial_DIN0207_L6.3mm_D2.5mm_P10.16mm_Horizontal
R3, R4, R6, R7, R8, R9: 100Ω; R_Axial_DIN0207_L6.3mm_D2.5mm_P10.16mm_Horizontal
R5, R11: 10kΩ; R_Axial_DIN0207_L6.3mm_D2.5mm_P10.16mm_Horizontal
R12: 1kΩ; R_Axial_DIN0207_L6.3mm_D2.5mm_P10.16mm_Horizontal
RV1: Synapse 1 Gain; Spikeling Potentiometer
RV2: Synapse 2 Gain; Spikeling Potentiometer
RV3: Voltage Membrane; Spikeling Potentiometer
RV4: Noise; Spikeling Potentiometer
RV5: Photodiode Gain; Spikeling Potentiometer
RV6: Stimulus Strength; Spikeling Potentiometer
RV7: Stimulus Frequency; Spikeling Potentiometer
SW1: Mode Button; SW_PUSH_6mm_H13mm
SW2: Buzzer Button; Spikeling reset button
SW3: Reset Button; Spikeling reset button
U1: ESP32-DEVKITC-32D; MODULE_ESP32-DEVKITC-32D; PARTREV 4
U2, U3: MCP3208; DIP-16_W7.62mm
U4: MCP23008; DIP-20_W7.62mm
U5: OPA380; SOIC-8_3.9x4.9mm_P1.27mm

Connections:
A_Axon: R1.1, U1.10 (IO26)
A_Current: J4.R, U3.4 (CH3)
A_Noise: RV4.2, U2.7 (CH6)
A_PD: RV5.2, U2.4 (CH3)
A_PhotoDiode: U3.3 (CH2), U5.6
A_Stim: J5.R, U1.9 (IO25)
A_StimFre: RV7.2, U2.6 (CH5)
A_StimStre: RV6.2, U2.5 (CH4)
A_Syn1: RV1.2, U2.2 (CH1)
A_Syn2: RV2.2, U2.3 (CH2)
A_Synapse1: J2.R, U3.1 (CH0)
A_Synapse2: J3.R, U3.2 (CH1)
A_Vm: RV3.2, U2.1 (CH0)
Button_Buzzer: R11.1, SW2.1, U4.12 (GP0)
Button_Mode: R5.1, SW1.1, U4.13 (GP1)
CLK: U1.28 (IO18), U2.13 (CLK), U3.13 (CLK), U4.1 (SCL)
CS_ADC1: U1.33 (IO0), U2.10 (~CS/SHDN)
CS_ADC2: U1.32 (IO4), U3.10 (~CS/SHDN)
CS_D1: U1.29 (IO5), U4.7 (CS)
CharliePlex1: R6.1, U4.19 (GP7)
CharliePlex2: R7.1, U4.18 (GP6)
CharliePlex3: R8.1, U4.17 (GP5)
CharliePlex4: R9.1, U4.16 (GP4)
D_Axon: J1.T, U4.15 (GP3)
D_Stim: R3.1, U4.14 (GP2)
D_Synapse1: J2.T, U1.34 (IO2)
D_Synapse2: J3.T, U1.35 (IO15)
GNDREF: BZ1.2 (+), C1.1, C2.1, C3.2, C4.2, C5.2, D0.2 (A), J1.S, J2.S, J3.S, J4.S, J5.S, R2.1, R4.2, R5.2, R11.2, R12.2, RV1.1, RV2.1, RV3.1, RV4.1, RV5.1, RV6.1, RV7.1, SW3.1, U1.14 (GND1), U1.20 (GND3), U1.26 (GND2), U2.9 (DGND), U2.14 (AGND), U3.9 (DGND), U3.14 (AGND), U4.4 (A1), U4.5 (A0), U4.9 (VSS), U5.3 (+), U5.4 (V-)
MISO: U1.27 (IO19), U2.12 (Dout), U3.12 (Dout), U4.3 (SO)
MOSI: U1.21 (IO23), U2.11 (Din), U3.11 (Din), U4.2 (SI)
unnamed: C3.1, J1.R, R1.2
unnamed: C4.1, D0.1 (K), R2.2, U5.2 (-)
unnamed: D1.2 (K), R4.1
unnamed: D4.1 (K), D5.2 (A), D6.2 (A), D7.1 (K), D8.1 (K), D9.2 (A), R8.2
unnamed: D2.1 (K), D3.2 (A), D4.2 (A), D5.1 (K), D10.2 (A), D11.1 (K), R7.2
unnamed: D6.1 (K), D7.2 (A), D10.1 (K), D11.2 (A), D12.1 (K), D13.2 (A), R9.2
unnamed: D2.2 (A), D3.1 (K), D8.2 (A), D9.1 (K), D12.2 (A), D13.1 (K), R6.2
unnamed: D14.2 (K), R12.1
unnamed: J5.T, R3.2
unnamed: SW3.2, U1.2 (EN)
Spike: BZ1.1 (-), U1.8 (IO33)
Spike_B: D1.4 (BA), U1.13 (IO12)
Spike_G: D1.3 (GA), U1.12 (IO14)
Spike_R: D1.1 (RA), U1.11 (IO27)
Stim_B: D14.4 (BA), U1.5 (IO34)
Stim_G: D14.3 (GA), U1.7 (IO32)
Stim_R: D14.1 (RA), U1.6 (IO35)
VCC: C1.2, C2.2, C5.1, RV1.3, RV2.3, RV3.3, RV4.3, RV5.3, RV6.3, RV7.3, SW1.2, SW2.2, U1.1 (3V3), U2.15 (Vref), U2.16 (Vdd), U3.15 (Vref), U3.16 (Vdd), U4.20 (VDD), U5.7 (V+)

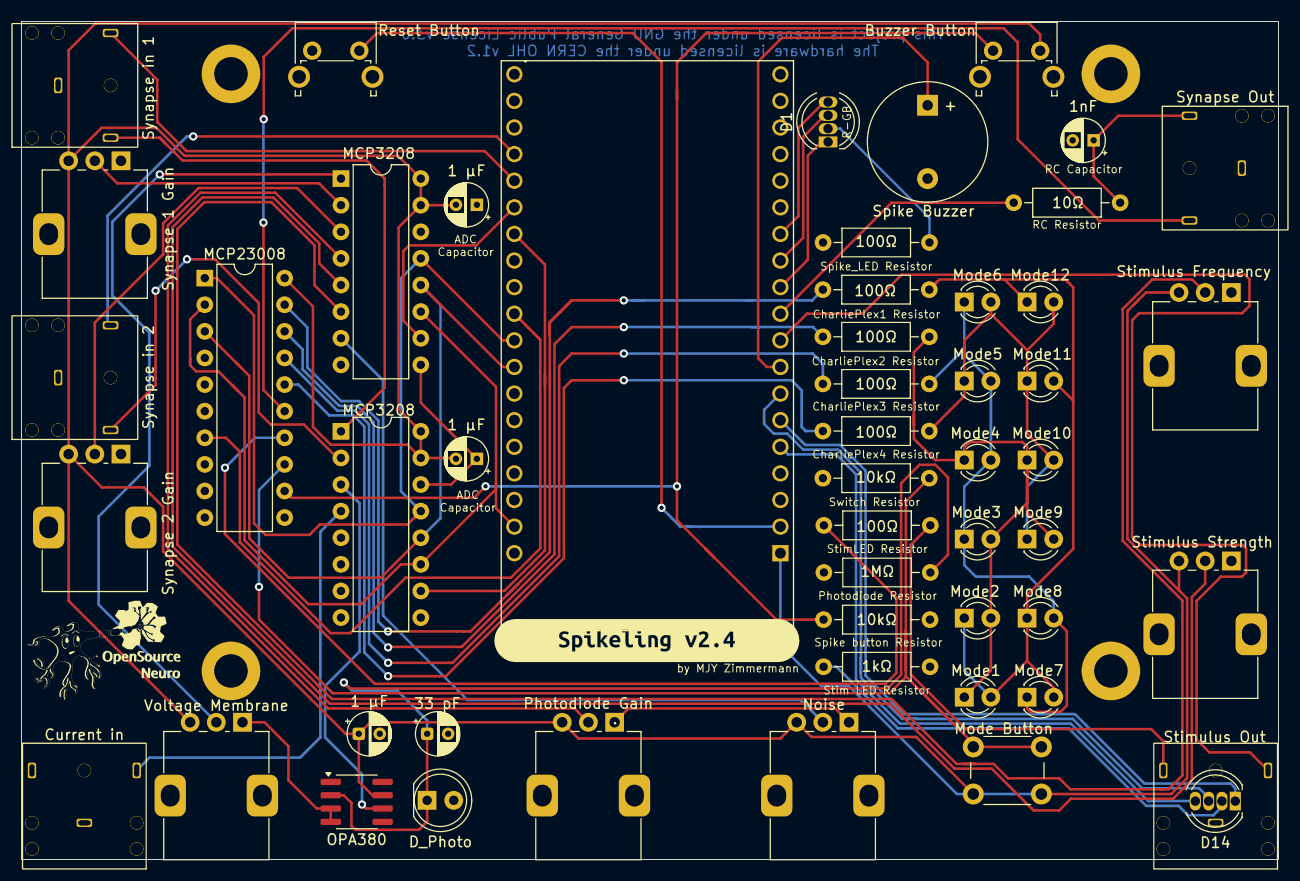
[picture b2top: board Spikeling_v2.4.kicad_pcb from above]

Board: 2 copper layers, 120.0 x 80.0 mm, 59 parts (0 on the bottom side), 48 nets.

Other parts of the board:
 : MountingHole_3.2mm_M3_DIN965_Pad
 #2: MountingHole_M3; MountingHole_3.2mm_M3_DIN965_Pad
 #3,  #4: MountingHole_3.2mm_M3_DIN965_Pad
.: Spikeling_neuron; Spikeling_Photoreceptor
.#2: Spikeling_neuron; Spikeling_Neuron
kibuzzard-668F87C1: G***; kibuzzard-668F87C1

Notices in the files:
PCB/Spikeling 3.0/Spikeling_v3.0.kicad_sch:
Licensed under CERN OHL v1.3
